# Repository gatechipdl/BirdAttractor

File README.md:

# BirdAttractor

## Requirements
- 5V Power input from in USB-B female form
- Two 5V Power output in USB-A female form
- Relay to control flow of at least 2A. Possibly more current support for better generalization. Most usb battery chargers are 2A, but some do 3A or 4A.
- Transistors to ensure relay coils trigger from MCU pins. ESP8266 can only drive 12mA on GPIO pins. Relays need >20mA.
 
- Ability to put microcontroller into deep sleep, waking up every 15 seconds to check for updates.
- Infinite alarms for super customization. Not interrupt based, only 15 second accuracy, due to deep sleep wakeup cycle.
- Ability to set the wakeup cycle from 1 second to 5 minutes. ESP8266 GPIO16 pulls CH-DP low during deep sleep. Anything that pulls 
 
- Microcontroller Interrupts for wakeup from deep sleep. ESP8266 can do this from the RTC on GPIO16 connected to reset.
- Two daily alarms for on and off settings. Interrupt based. The alarm interrupt on DS3231 only pulls down to 3mA, so it might need a transistor to boost the current capability to overcome the GPIO16 high signal when in deep_sleep.
 
- FTDI header pins with TX,RX,GND,5V for programming (could be removed if we can program using pogo pins and the firmware is completely debugged).
- Button to control Reset for programming. Button should ideally be hardware debounced, but could probably work without it. ESP8266 needs to pull Reset low, and then GPIO0 low to enter programming mode.
 
- Button to activate Wi-Fi for configuration.
- LED to notify users that the Wi-Fi is on. Should draw less than 12mA.
- LED to show that power is coming in. Should draw less than 12mA.
- LED to show that output power is switched on. Should draw less than 12mA.
 
- Voltage regulator to bring down 5V input to 3.3V for electronics. Should have decoupling capacitors to smooth the supply.
 
- Photoresistor to detect the amount of light for use as a trigger.
-- Ability to configure light based alarm. Five minute response time is sufficient.

- Temperature sensor. Can use the temperature sensor inside the TCXO RTC, which can be good enough.
 
- Real Time Clock with a temperature compensated crystal oscillator (TCXO).
-- Real Time Clock with sub 0C and very high temperature range with high accuracy.
-- Ability to set the timezone on the RTC.
-- Ability to push time from Wi-Fi connected device onto the MCU to update the RTC.

- Record the last X number of light and temperature readings along with when the power was turned on and off, and the timestamp.
-- Option to set the frequency of saving of readings.
-- Option to save X number of samples or to record until there is still memory available.
-- Option to cycle through the available memory or just stop recording when full.
-- Option to reset the samples by clearing the cache.
-- Option to visualize the data in a chart on the web interface.
-- Option to download the data to a Wi-Fi connected web client.
 
---------------
## LED
- Blue LED
- 150080BS75000
- Package:0805
- Forward Voltage: 3.2V
- Max Current: 20mA
- Current Limiting Resistor at 12mA: 16.6 ohms (E12=18 ohms or 22 ohms)
- $0.29@1, digi-key
- $0.23@100, digi-key

---------------
## RTC

### DS1305
- Arduino Library: https://github.com/cjbearman/ds1305-arduino
- Alarms:2
- has two alarms, each alarm must be reset by a read or write to the Alarm interrupt register. Must use an MCU to do this.
- The INT0 and INT1 interrupt output pins are pulled low, so when the alarm asserts, we have to have a pull-up resistor to bring the value up.
- It is likely the INT0 and INT1 pins may not be able to sink enough current to have a small pull up resistor. So with a larger value pull up resistor, the provided current on alarm assertion will be small as well. To magnify this current, a MOSFET may be needed.

### DS1307
- Arduino Library: DS1307RTC, Rtc by Makuna, RTCx 
- TXCO:No, not accurate enough

### DS3231
-Arduino Library: Rtc by Makuna, Sodaq_DS3231
#### DS3231SN
- has temperature compensated crystal oscillator (may need this for cold temps)
- TCXO:Yes
- Alamrs:2
- $9.97@1, digi-key
- $6.59@100, digi-key
- $2.50@10, aliexpress
#### DS3231M
- TCXO: unclear
- $6.46@1, digi-key
- $4.801@50, digi-key

### PCF2129
- TCXO:yes
- Arduino Library: FaBo 215 RTC PCF2129
#### PCF2129T
- Package:16-SOIC
- Temp:-30C to +80C
- $3.36@1, digi-key
- $2.47@100, digi-key
#### PCF2129AT
- Package:20-SOIC, similar as 16-SOIC but with 4 NC pins
- Temp:-15C to +60C
- $2.92@1, digi-key
- $2.15@100, digi-key

### PCF2127
- TXCO:Yes
- Arduino Library: I2C-Sensor-Lib iLib
- includes 512 bytes of general-purpose static RAM
#### PCF2127T
- Package:16-SOIC
- Temp:-30C to +80C
- $4.01@1, digi-key
- $2.95@100, digi-key
#### PCF2127AT
- Package:20-SOIC
- Temp:-15C to +60C
- $3.60@1, digi-key
- $2.65@100, digi-key
 
### PCA2129
- Arduino Library: None Found
- TXCO:Yes
#### PCA2129T
- Package:16-SOIC
- Temp:-30C to +80C
- $4.70@1, digi-key
- $3.46@100, digi-key

### MCP79400
- TXCO:No
- Arduino Library: RTCx (includes MCP7941x)
- accuracy potentially better than ds1307 and pcf8563, but not ds3231
- $0.82@1, digi-key
- $0.72@100, digi-key

---------------
## Relay
- latching, dual coil, bistable
- contact current: 2,3-10 Amps (2A seems an industry threshold)
- coil voltage: 3.3V,5V
- coil current: <100mA
- switching voltage: >5VDC

### V23079
- Current:2A
#### V23079-E1201-B301
- Signal Volage:3.75V-5V
- Signal Current:28mA
- Latching:Yes
- Bistable:Yes
- $3.69@1, digi-key
- $2.77@100, digi-key
#### V23079-A1001-B301
- $5.17@10, aliexpress
- Monstable:Yes
- Bistable:No
- standard coil, coil 001
- standard version, 2 form C contacts

### TX2SA
#### TX2SA-LT-5V-TH-Z
- Signal Volage:5V
- Signal Current:28.1mA
- Current:2A
- $5.83@1, digi-key
- $4.38@100, digi-key

### G6BK (5A, twice as expensive as 2A)
#### G6BK-1114P-US-DC5
- Signal Voltage:5V
- Signal Current:56mA
- Current:5A
- $7.61@1, digi-key
- $5.71@100, digi-key

### AQV25
- Type:solid state
### AQV251G
- Package:6-DIP
- Current:3.5A
- Voltage:0-30V
- $7.75@1, digi-key
- $5.85@100, digi-key
### AQV252G
- Package:6-SOIC
- Current:2.5A
- Voltage:0-60V
#### AQV252GAX
- Tape and Reel packaging on 123 pin side
- $5.39@1, digi-key
- $4.04@100, digi-key
#### AQV252GAZ
- Tape and Reel packaging on 456 pin side
#### AQV252GA
- Tube packing style

---------------
## Coin Cell Retainer/Holder
- Battery:CR2032
- Battery Diameter:20mm
### BU2032
#### BU2032-1-HD-G
- Type:through hole holder
- $0.83@1, digi-key
- $0.69@100, digi-key
#### BU2032SM-HD-G
- Type:surface mount holder
- $0.87@1, digi-key
- $0.76@100, digi-key
### BK
#### BK-913
- Type:through hole retainer
- Notes:easy replacement
- $0.35@1, digi-key
- $0.30@100, digi-key
#### BK-888
- Type:through hole retainer
- blocks inner side
- easy replacement
- $0.39@1, digi-key
- $0.33@100, digi-key

---------------
## LDO
- needed for running the esp8266 microprocessor
### AMS1117-3.3
- Package:SOT-223
- $1.58@50, aliexpress

---------------
## MCU
### ESP8266
- Wi-Fi:Yes
- Allows us to have a Wi-Fi interface for setting the time and other settings.
- VCC:3.3V
- Runs on 3.3V, so should have an LDO or similar to bring down the 5V supply.
- Should only be turned in two instances. First is to creating the Wi-Fi interface. Second is at an alarm, to turn off the alarm, and then shut itself down. If we use deep sleep, then we could check every 5 minutes (or less) to see if the alarm pin is pulled high.
- It might be possible to use the reset pin on the ESP8266 to wake it up with the alarm. This would be more power efficient and have better reaction time (within milliseconds) to the alarm assertion, but the solution is more complex and takes longer to develop. https://github.com/esp8266/Arduino/issues/1488
- pin mapping: http://www.esp8266.com/wiki/doku.php?id=esp8266_gpio_pin_allocations

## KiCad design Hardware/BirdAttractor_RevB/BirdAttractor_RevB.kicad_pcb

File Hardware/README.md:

RevA - first version
RevB - with correct parts, and partial design for in house milling; through hole parts flipped to bottom
RevC - layout with parts on top for fab house milling
 - problems
 -- smd button melts with 800 degree heat
 -- through-hole 6mm button legs don't fit well into holes
 -- missing a few 1206 sized resistors
 -- battery backwards due to kicad default battery pinout
 -- battery rotated backwards too on board; curved portion is where button slides in
 -- some LEDs on by default; check that is correct; should be able to disable
 -- relays are only monostable, not latching; only has one input; ok bc can be compensated for in code
 -- relays are throughole; should design for smd and tht too

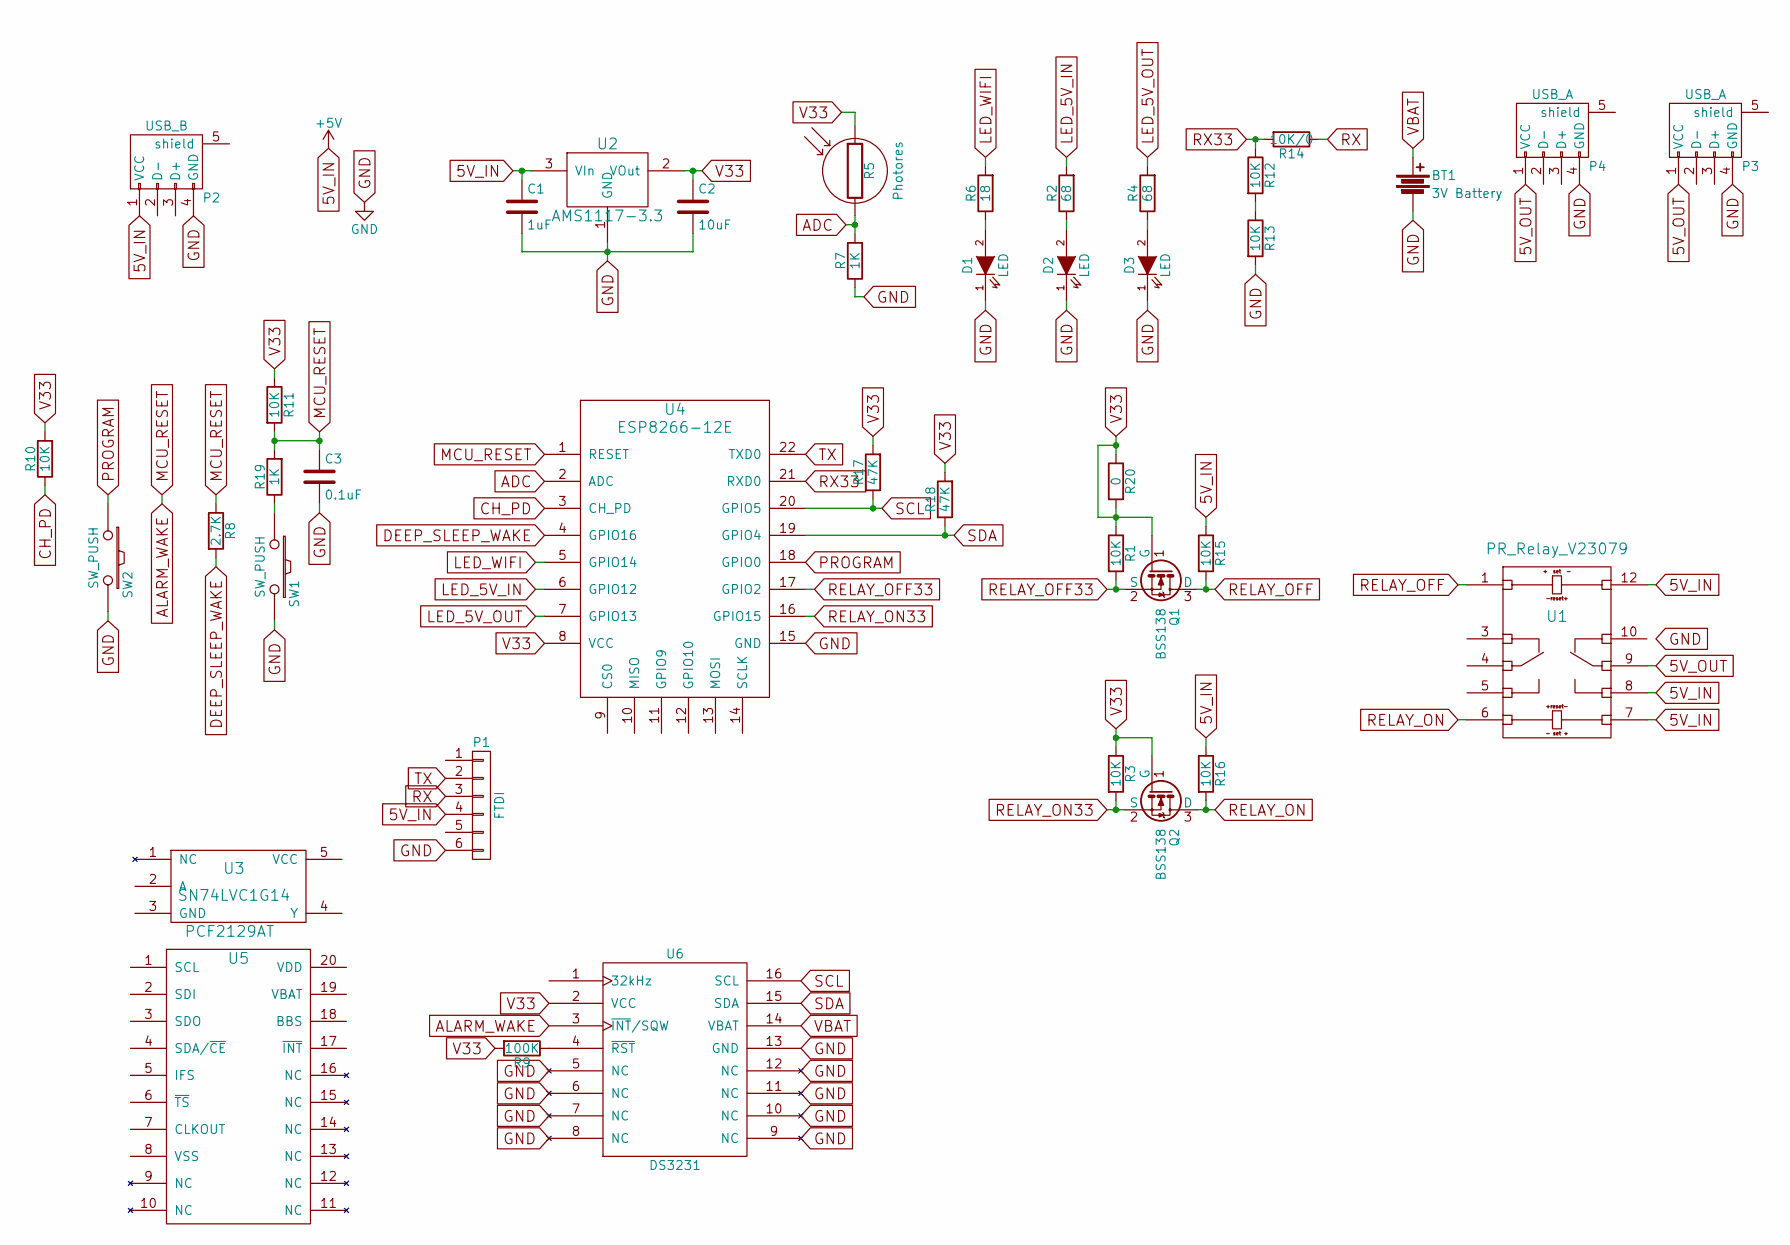
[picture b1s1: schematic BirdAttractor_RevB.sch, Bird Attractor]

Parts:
BT1: 3V Battery; BU2032-1-HD-G
C1: 1uF; C_0805
C2: 10uF; C_0805
C3: 0.1uF; C_0805
D1, D2, D3: LED; LED-0805
P1: FTDI; Pin_Header_Angled_1x06
P2: USB_B
P3, P4: USB_A
Q1, Q2: BSS138; SOT-23
R1, R3, R12, R13, R15, R16: 10K; R_1206
R2, R4: 68; C_1206
R5: Photores; LED-3MM
R6: 18; C_1206
R7, R19: 1K; C_1206
R8: 2.7K; C_1206
R9: 100K; C_1206
R10, R11: 10K; C_1206
R14: 10K/0; R_1206
R17, R18: 47K; C_1206
R20: 0; R_1206
SW1, SW2: SW_PUSH; SW_SPST_PTS645
U1: PR_Relay_V23079; DIP-12-SMD
U2: AMS1117-3.3; SOT-223
U3: SN74LVC1G14; SOT-23-5-80
U4: ESP8266-12E; ESP8266-12E-80
U5: PCF2129AT; SOIC-20_7.5x12.8mm_Pitch1.27mm-80
U6: DS3231; SO-16-W

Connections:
5V_IN: C1.1, P1.4, P2.1 (VCC), R15.1, R16.1, U1.7, U1.8, U1.12, U2.3 (VIn)
5V_OUT: P3.1 (VCC), P4.1 (VCC), U1.9
ADC: R5.2, R7.2, U4.2 (ADC)
ALARM_WAKE: C3.1, R8.1, R11.2, R19.2, U4.1 (RESET), U6.3 (~INT~/SQW)
CH_PD: R10.1, U4.3 (CH_PD)
DEEP_SLEEP_WAKE: R8.2, U4.4 (GPIO16)
GND: BT1.2, C1.2, C2.2, C3.2, D1.1 (K), D2.1 (K), D3.1 (K), P1.6, P2.4 (GND), P3.4 (GND), P4.4 (GND), R7.1, R13.2, SW1.2, SW2.2, U2.1 (GND), U4.15 (GND), U6.5 (NC), U6.6 (NC), U6.7 (NC), U6.8 (NC), U6.9 (NC), U6.10 (NC), U6.11 (NC), U6.12 (NC), U6.13 (GND)
LED_5V_IN: R2.2, U4.6 (GPIO12)
LED_5V_OUT: R4.2, U4.7 (GPIO13)
LED_WIFI: R6.2, U4.5 (GPIO14)
unnamed: D1.2 (A), R6.1
unnamed: D2.2 (A), R2.1
unnamed: D3.2 (A), R4.1
unnamed: R9.1, U6.4 (~RST)
unnamed: R12.2, R13.1
unnamed: R19.1, SW1.1
PROGRAM: SW2.1, U4.18 (GPIO0)
RELAY_OFF: Q1.3 (D), R15.2, U1.1
RELAY_OFF33: Q1.2 (S), R1.2, U4.17 (GPIO2)
RELAY_ON: Q2.3 (D), R16.2, U1.6
RELAY_ON33: Q2.2 (S), R3.2, U4.16 (GPIO15)
RX: P1.3, R14.1
RX33: R12.1, R14.2, U4.21 (RXD0)
SCL: R17.1, U4.20 (GPIO5), U6.16 (SCL)
SDA: R18.1, U4.19 (GPIO4), U6.15 (SDA)
TX: P1.2, U4.22 (TXD0)
V33: C2.1, Q1.1 (G), Q2.1 (G), R1.1, R3.1, R5.1, R9.2, R10.2, R11.1, R17.2, R18.2, R20.1, R20.2, U2.2 (VOut), U4.8 (VCC), U6.2 (VCC)
VBAT: BT1.1, U6.14 (VBAT)

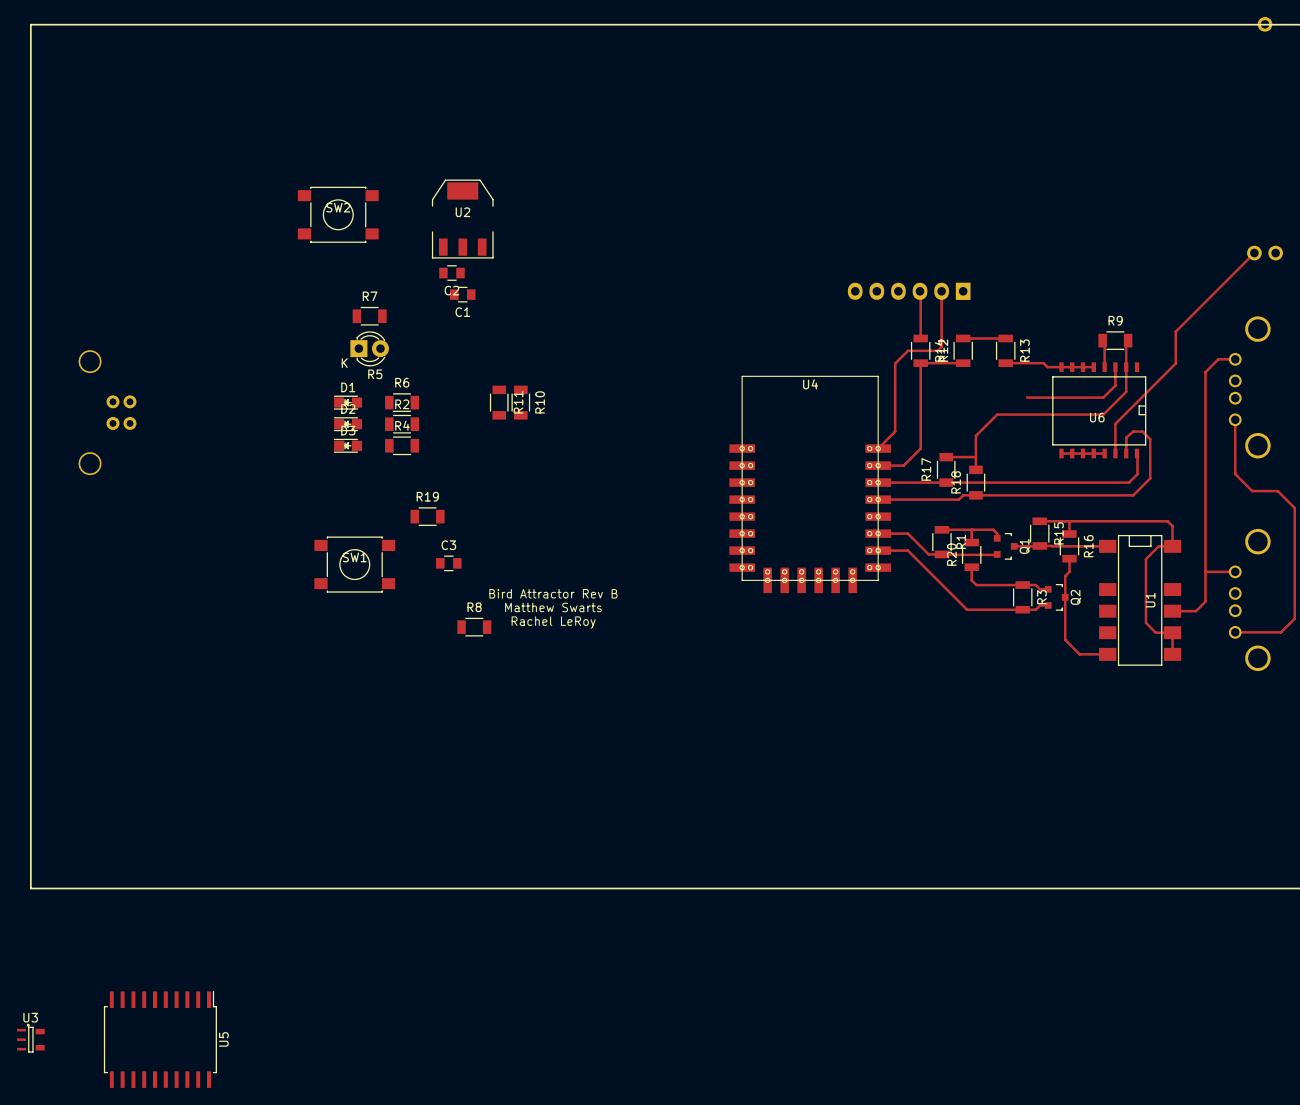
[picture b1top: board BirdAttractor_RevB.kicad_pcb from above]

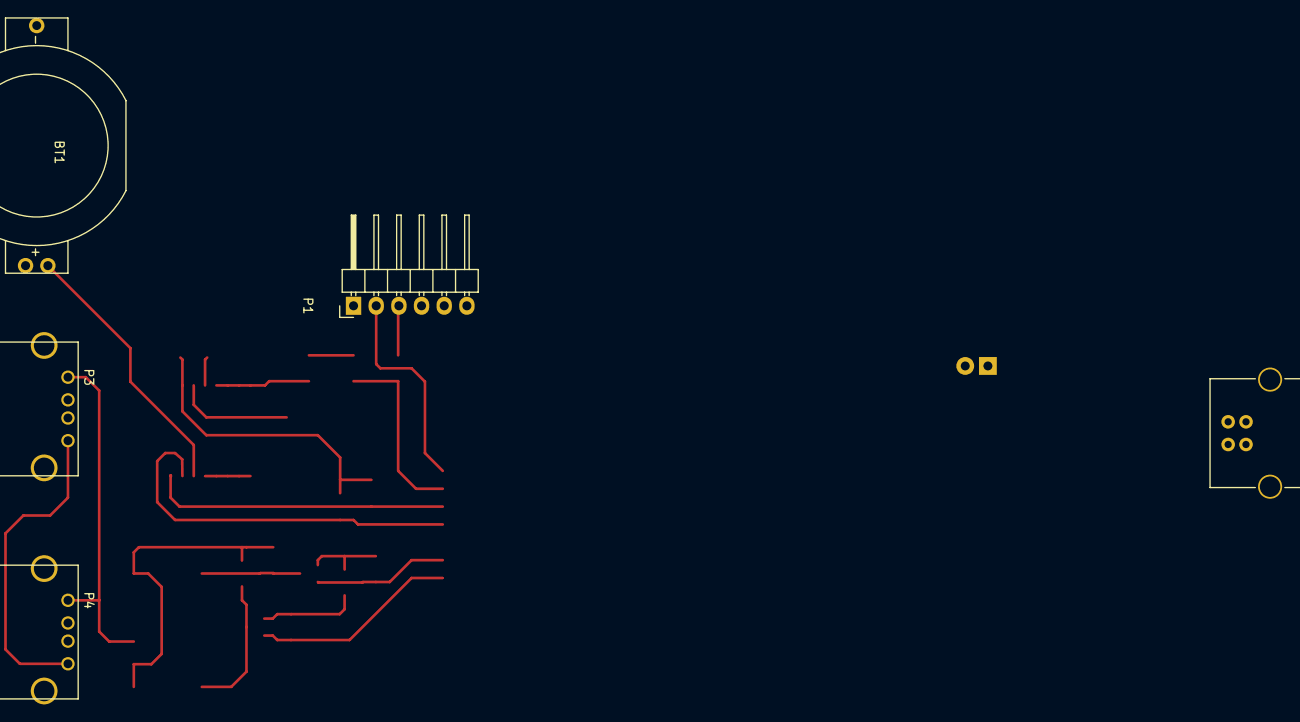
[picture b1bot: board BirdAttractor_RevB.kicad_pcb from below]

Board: 2 copper layers, 41 parts (5 on the bottom side), 28 nets.

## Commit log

2016-09-13 added hardware files
2016-09-26 added some notes on the rtc
2016-10-12 added notes on parts in readme, added new revision to the board with newly selected parts
2016-10-14 added more components and more notes in the readme
2016-10-15 added low pass debounce filter, added connections for different wake up functions, began layout design for in house pcb.
2016-10-16 minor updates
2016-10-25 added pull down resistor to gpio15 for programming; created RevC and board ready for fabrication
2016-11-30 added models and software
2016-12-05 added photo of Rev C board assembled listed problems with Rev C board to be addressed in the next version.

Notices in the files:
Hardware/BirdAttractor_RevB/BirdAttractor_RevB.kicad_pcb:
MIT License
